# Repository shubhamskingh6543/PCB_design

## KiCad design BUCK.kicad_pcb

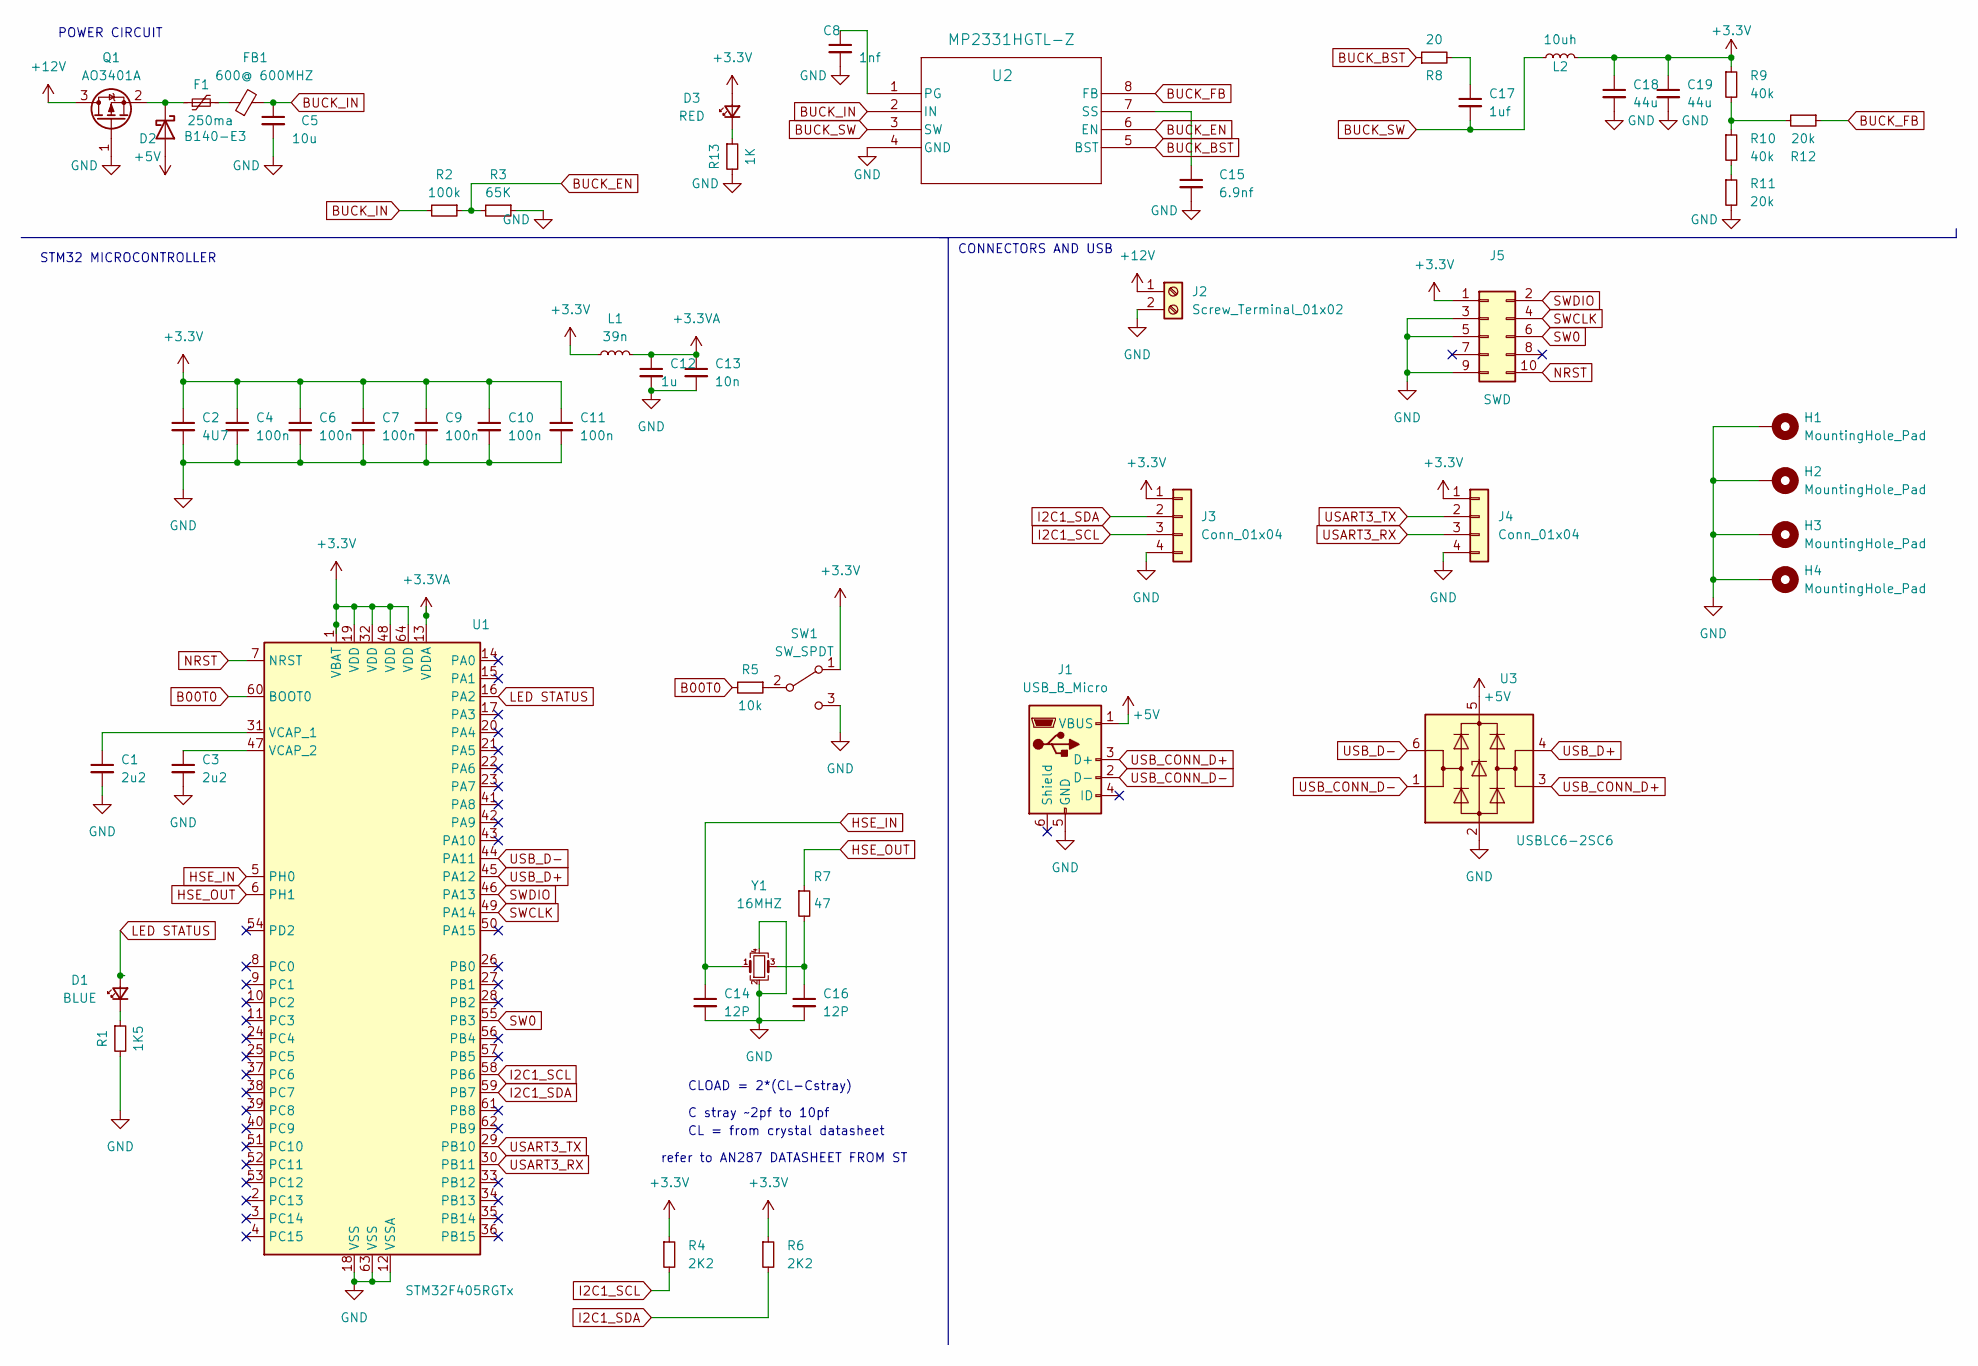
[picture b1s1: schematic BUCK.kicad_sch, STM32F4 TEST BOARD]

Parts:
C1, C3: 2u2; C_0603_1608Metric
C2: 4U7; C_0603_1608Metric
C4, C6, C7, C9, C10, C11: 100n; C_0402_1005Metric
C5: 10u; C_1206_3216Metric
C8: 1nf; C_1206_3216Metric
C12: 1u; C_0402_1005Metric
C13: 10n; C_0402_1005Metric
C14, C16: 12P; C_0402_1005Metric
C15: 6.9nf; C_1206_3216Metric
C17: 1uf; C_1206_3216Metric
C18, C19: 44u; C_1206_3216Metric
D1: BLUE; LED_0201_0603Metric
D2: B140-E3; D_SMA
D3: RED; LED_0201_0603Metric
F1: 250ma; Fuse_1206_3216Metric
FB1: 600@ 600MHZ; L_0805_2012Metric
H1, H2, H3, H4: MountingHole_Pad; MountingHole_4.3mm_M4_Pad_Via
J1: USB_B_Micro; USB_Mini-B_Wuerth_65100516121_Horizontal
J2: Screw_Terminal_01x02; TerminalBlock_Phoenix_PT-1,5-2-3.5-H_1x02_P3.50mm_Horizontal
J3, J4: Conn_01x04; Molex_PicoBlade_53048-0410_1x04_P1.25mm_Horizontal
J5: SWD; PinSocket_2x05_P1.27mm_Vertical_SMD
L1: 39n; L_0402_1005Metric
L2: 10uh; L_Sunlord_MWSA05xxS
Q1: AO3401A; SOT-23
R1: 1K5; R_0603_1608Metric
R2: 100k; R_0603_1608Metric
R3: 65K; R_0603_1608Metric
R4, R6: 2K2; R_0603_1608Metric
R5: 10k; R_0402_1005Metric
R7: 47; R_0402_1005Metric
R8: 20; R_0603_1608Metric
R9, R10: 40k; R_0603_1608Metric
R11, R12: 20k; R_0603_1608Metric
R13: 1K; R_0603_1608Metric
SW1: SW_SPDT; SW_SPDT_PCM12
U1: STM32F405RGTx; LQFP-64_10x10mm_P0.5mm
U2: MP2331HGTL-Z; SOT583_MP2331H
U3: USBLC6-2SC6; SOT-23-6
Y1: 16MHZ; Crystal_SMD_3225-4Pin_3.2x2.5mm

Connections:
+3.3V: C2.1, C4.1, C6.1, C7.1, C9.1, C10.1, C11.1, C18.1, C19.1, D3.2 (A), J3.1, J4.1, J5.1, L1.1, L2.2, R4.1, R6.1, R9.1, SW1.1 (A), U1.1 (VBAT), U1.19 (VDD), U1.32 (VDD), U1.48 (VDD), U1.64 (VDD)
+3.3VA: C12.1, C13.1, L1.2, U1.13 (VDDA)
+5V: D2.2 (A), J1.1 (VBUS), U3.5 (VBUS)
+12V: J2.1, Q1.3 (D)
B00T0: R5.2, U1.60 (BOOT0)
BUCK_BST: R8.1, U2.5 (BST)
BUCK_EN: R2.1, R3.2, U2.6 (EN)
BUCK_FB: R12.1, U2.8 (FB)
BUCK_IN: C5.1, FB1.2, R2.2, U2.2 (IN)
BUCK_SW: C17.2, L2.1, U2.3 (SW)
GND: C1.2, C2.2, C3.2, C4.2, C5.2, C6.2, C7.2, C8.2, C9.2, C10.2, C11.2, C12.2, C13.2, C14.2, C15.2, C16.2, C18.2, C19.2, H1.1, H2.1, H3.1, H4.1, J1.5 (GND), J2.2, J3.4, J4.4, J5.3, J5.5, J5.9, Q1.1 (G), R1.2, R3.1, R11.2, R13.2, SW1.3 (C), U1.12 (VSSA), U1.18 (VSS), U1.63 (VSS), U2.4 (GND), U3.2 (GND), Y1.2, Y1.4
HSE_IN: C14.1, U1.5 (PH0), Y1.1
HSE_OUT: R7.1, U1.6 (PH1)
I2C1_SCL: J3.3, R4.2, U1.58 (PB6)
I2C1_SDA: J3.2, R6.2, U1.59 (PB7)
LED STATUS: D1.2 (A), U1.16 (PA2)
NRST: J5.10, U1.7 (NRST)
unnamed: C1.1, U1.31 (VCAP_1)
unnamed: C3.1, U1.47 (VCAP_2)
unnamed: C8.1, U2.1 (PG)
unnamed: C15.1, U2.7 (SS)
unnamed: C16.1, R7.2, Y1.3
unnamed: C17.1, R8.2
unnamed: D1.1 (K), R1.1
unnamed: D2.1 (K), F1.1, Q1.2 (S)
unnamed: D3.1 (K), R13.1
unnamed: F1.2, FB1.1
unnamed: R5.1, SW1.2 (B)
unnamed: R9.2, R10.1, R12.2
unnamed: R10.2, R11.1
SW0: J5.6, U1.55 (PB3)
SWCLK: J5.4, U1.49 (PA14)
SWDIO: J5.2, U1.46 (PA13)
USART3_RX: J4.3, U1.30 (PB11)
USART3_TX: J4.2, U1.29 (PB10)
USB_CONN_D+: J1.3 (D+), U3.3 (I/O2)
USB_CONN_D-: J1.2 (D-), U3.1 (I/O1)
USB_D+: U1.45 (PA12), U3.4 (I/O2)
USB_D-: U1.44 (PA11), U3.6 (I/O1)

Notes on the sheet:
POWER CIRCUIT
refer to AN287 DATASHEET FROM ST
CONNECTORS AND USB
C stray ~2pf to 10pf
CL = from crystal datasheet
STM32 MICROCONTROLLER
CLOAD = 2*(CL-Cstray)

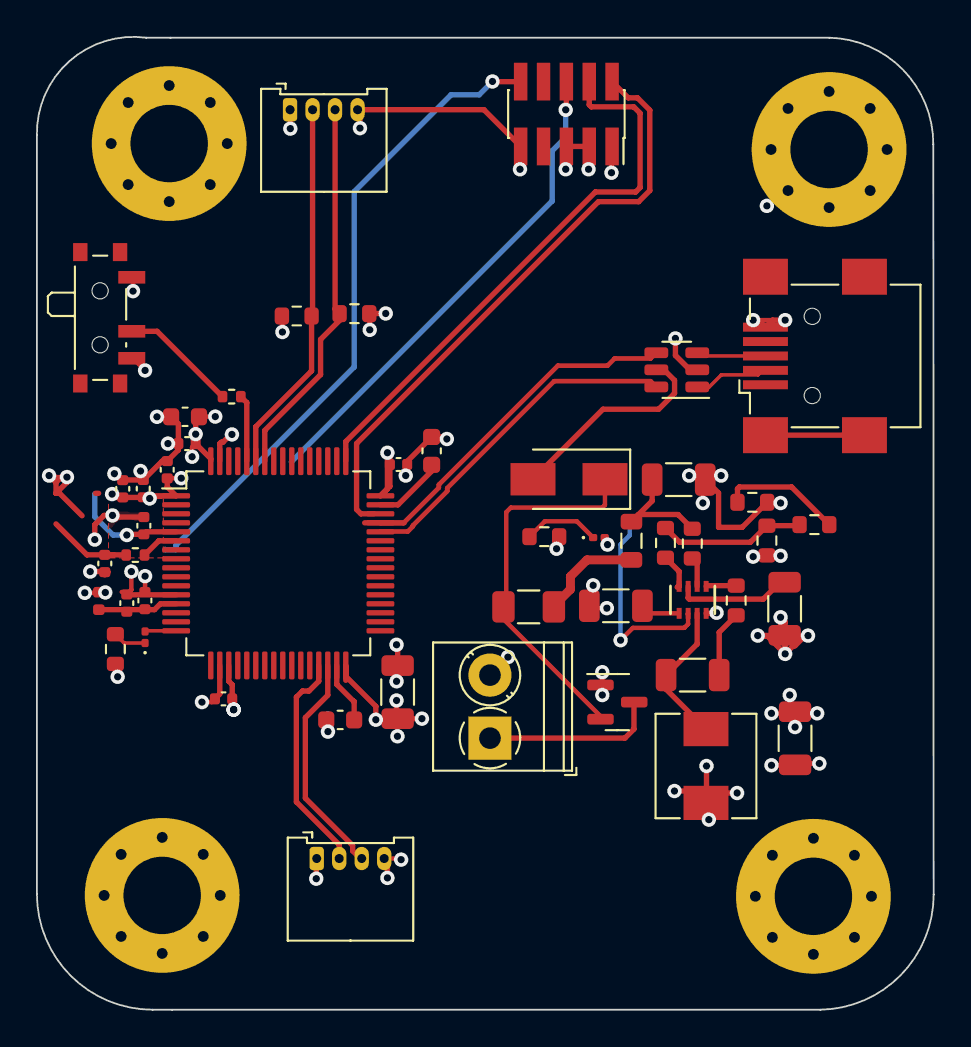
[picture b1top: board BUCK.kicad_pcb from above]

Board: 4 copper layers, 49.8 x 54.0 mm, 52 parts (0 on the bottom side), 39 nets.

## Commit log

2023-10-16 Version 1
